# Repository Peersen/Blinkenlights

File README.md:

# Blinkenlights

An Arduino Nano sending DMX to a Driver Chip making several Dimmerchannels blink in a random but controlled manner.
It uses four potentiometers controlling:
- overall Level
- speed of the fading lights
- range how far the lights fade out from Base LEvel
- the amount of lights doing crazy stuff

PCB
- one sided for home-etching
- Dip switch for dmx address
- selector jumper to switch between sending and receiving dmx
- spare poti connectors for later use
- I2C Pins
- reset Pins
- Screw terminals for Vin and 5v rail of the arduino and DMX signal from the SN75176 tranceiverchip

Other projects in this repository help to troubleshoot the main project
- a dmx receiver making six Leds blink
- a softwareSerial receiving arduino that sends received strings to the arduinos USB COM port

To Start
- if you use Platform IO: make sure to change " lib_extra_dirs = D:\ArduinoSketches\libraries" in PlatformIO.ini
- install DMXserial Librarie by Matthias Hertel:
  http://www.mathertel.de/Arduino/DMXSerial.aspx or https://github.com/mathertel/DmxSerial

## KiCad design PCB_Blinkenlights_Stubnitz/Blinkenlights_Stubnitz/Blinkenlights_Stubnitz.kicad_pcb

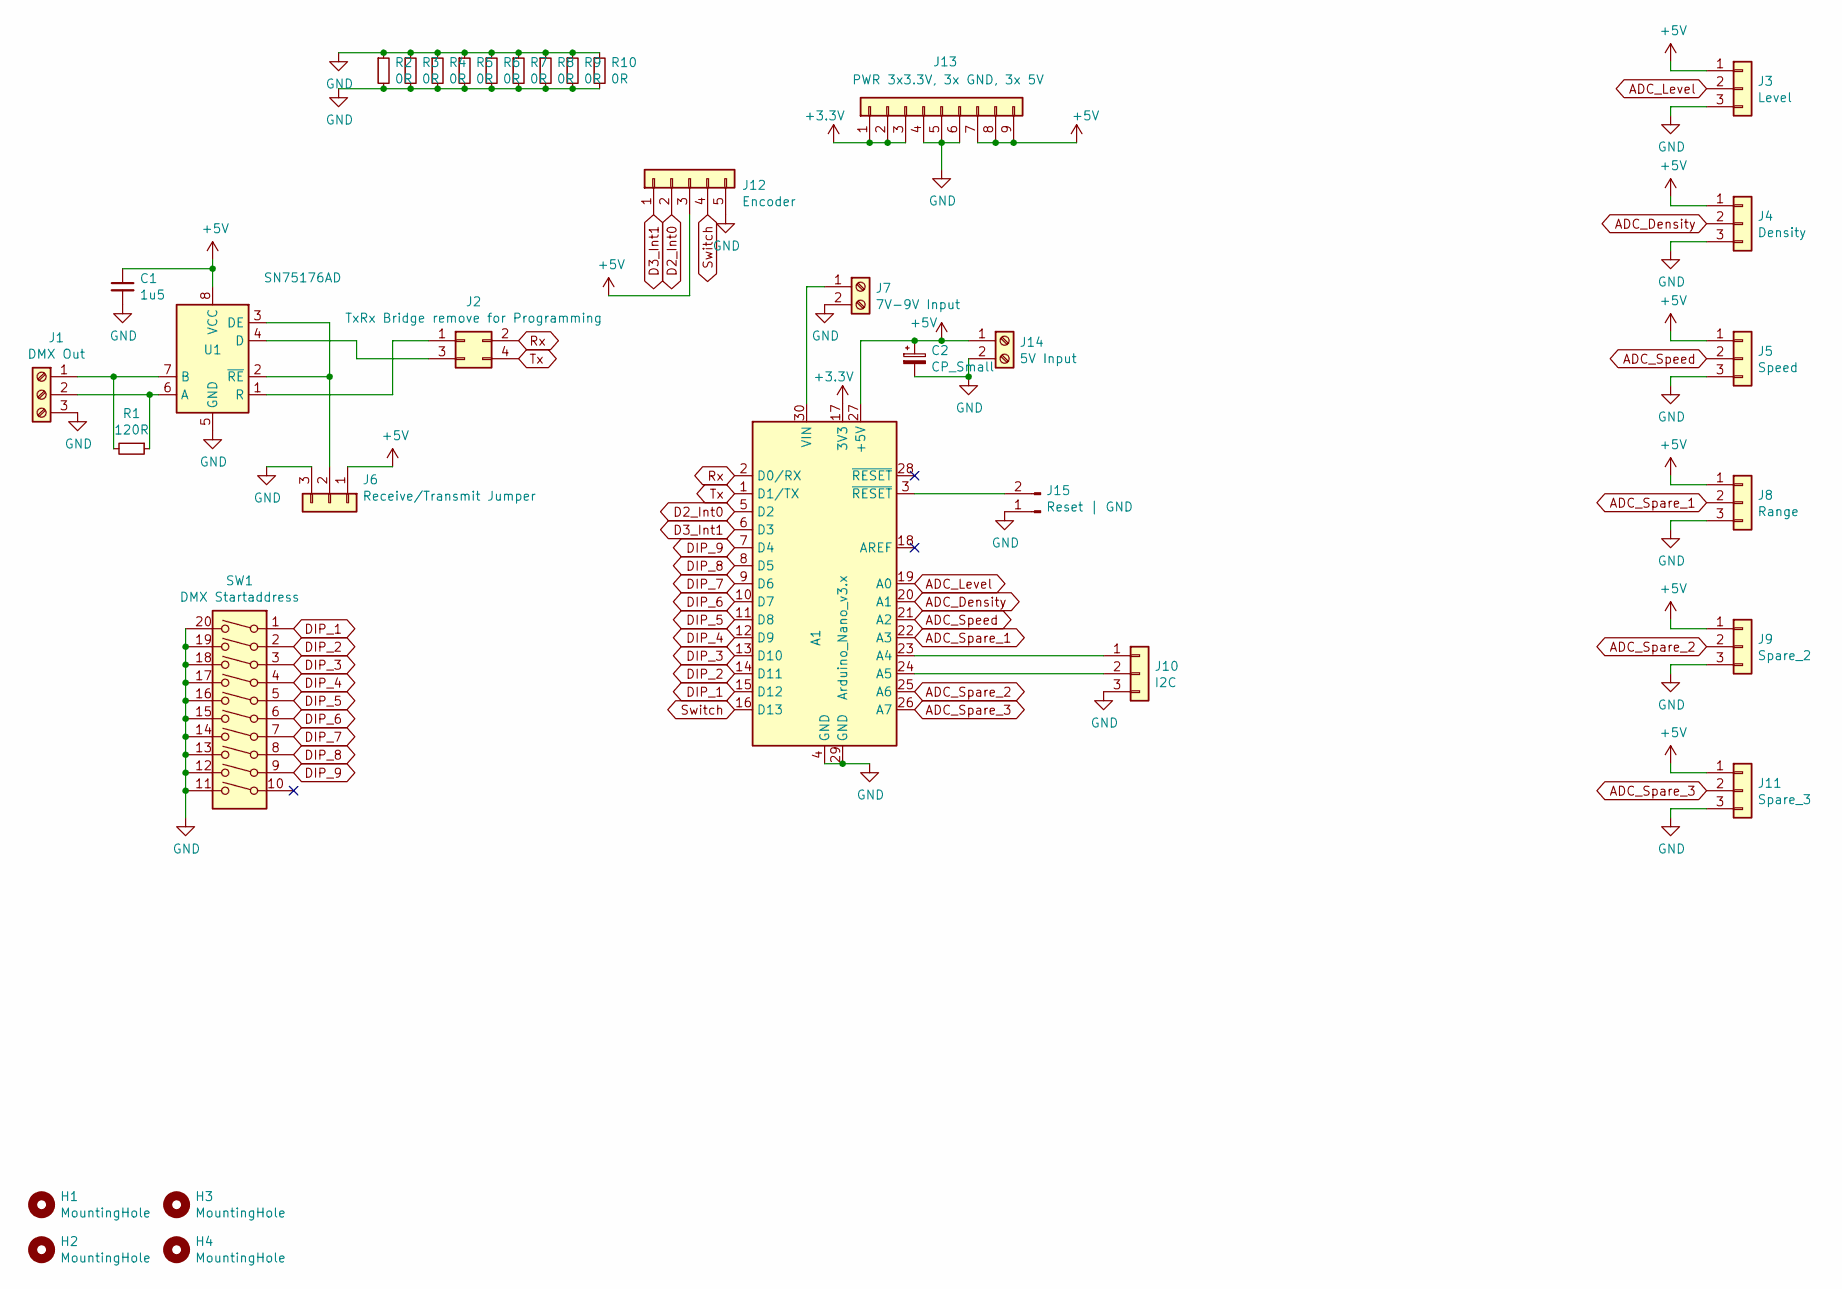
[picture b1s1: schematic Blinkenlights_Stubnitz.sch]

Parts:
A1: Arduino_Nano_v3.x; Arduino_Nano
C1: 1u5; C_1206_3216Metric_Pad1.42x1.75mm_HandSolder
C2: CP_Small; CP_Radial_D5.0mm_P2.50mm
H1, H2, H3, H4: MountingHole; MountingHole_3.2mm_M3_Pad
J1: DMX Out; TerminalBlock_bornier-3_P5.08mm
J2: TxRx Bridge remove for Programming; PinHeader_2x02_P2.54mm_Vertical
J3: Level; PinHeader_1x03_P2.54mm_Vertical
J4: Density; PinHeader_1x03_P2.54mm_Vertical
J5: Speed; PinHeader_1x03_P2.54mm_Vertical
J6: Receive/Transmit Jumper; PinHeader_1x03_P2.54mm_Vertical
J7: 7V-9V Input; TerminalBlock_bornier-2_P5.08mm
J8: Range; PinHeader_1x03_P2.54mm_Vertical
J9: Spare_2; PinHeader_1x03_P2.54mm_Vertical
J10: I2C; PinHeader_1x03_P2.54mm_Vertical
J11: Spare_3; PinHeader_1x03_P2.54mm_Vertical
J12: Encoder; PinHeader_1x05_P2.54mm_Vertical
J13: PWR 3x3.3V, 3x GND, 3x 5V; PinHeader_1x09_P2.54mm_Vertical
J14: 5V Input; TerminalBlock_bornier-2_P5.08mm
J15: Reset | GND; PinHeader_1x02_P2.54mm_Vertical
R1: 120R; R_1206_3216Metric_Pad1.42x1.75mm_HandSolder
R2, R3, R4, R5, R6, R7, R8, R9, R10: 0R; R_Axial_DIN0207_L6.3mm_D2.5mm_P10.16mm_Horizontal
SW1: DMX Startaddress; SW_DIP_SPSTx10_Slide_9.78x27.58mm_W7.62mm_P2.54mm
U1: SN75176AD; SOIC-8_3.9x4.9mm_P1.27mm

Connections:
+3V3: A1.17 (3V3), J13.1, J13.2, J13.3
+5V: A1.27 (+5V), C1.1, C2.1, J3.1, J4.1, J5.1, J6.1, J8.1, J9.1, J11.1, J12.3, J13.7, J13.8, J13.9, J14.1, U1.8 (VCC)
ADC_Density: A1.20 (A1), J4.2
ADC_Level: A1.19 (A0), J3.2
ADC_Spare_1: A1.22 (A3), J8.2
ADC_Spare_2: A1.25 (A6), J9.2
ADC_Spare_3: A1.26 (A7), J11.2
ADC_Speed: A1.21 (A2), J5.2
D2_Int0: A1.5 (D2), J12.2
D3_Int1: A1.6 (D3), J12.1
DIP_1: A1.15 (D12), SW1.1
DIP_2: A1.14 (D11), SW1.2
DIP_3: A1.13 (D10), SW1.3
DIP_4: A1.12 (D9), SW1.4
DIP_5: A1.11 (D8), SW1.5
DIP_6: A1.10 (D7), SW1.6
DIP_7: A1.9 (D6), SW1.7
DIP_8: A1.8 (D5), SW1.8
DIP_9: A1.7 (D4), SW1.9
GND: A1.4 (GND), A1.29 (GND), C1.2, C2.2, J1.3, J3.3, J4.3, J5.3, J6.3, J7.2, J8.3, J9.3, J10.3, J11.3, J12.5, J13.4, J13.5, J13.6, J14.2, J15.1, R2.1, R2.2, R3.1, R3.2, R4.1, R4.2, R5.1, R5.2, R6.1, R6.2, R7.1, R7.2, R8.1, R8.2, R9.1, R9.2, R10.1, R10.2, SW1.11, SW1.12, SW1.13, SW1.14, SW1.15, SW1.16, SW1.17, SW1.18, SW1.19, SW1.20, U1.5 (GND)
unnamed: A1.3 (~RESET), J15.2
unnamed: A1.23 (A4), J10.1
unnamed: A1.24 (A5), J10.2
unnamed: A1.30 (VIN), J7.1
unnamed: J1.1, R1.2, U1.7 (B)
unnamed: J1.2, R1.1, U1.6 (A)
unnamed: J2.1, U1.1 (R)
unnamed: J2.3, U1.4 (D)
unnamed: J6.2, U1.2 (~RE), U1.3 (DE)
Rx: A1.2 (D0/RX), J2.2
Switch: A1.16 (D13), J12.4
Tx: A1.1 (D1/TX), J2.4

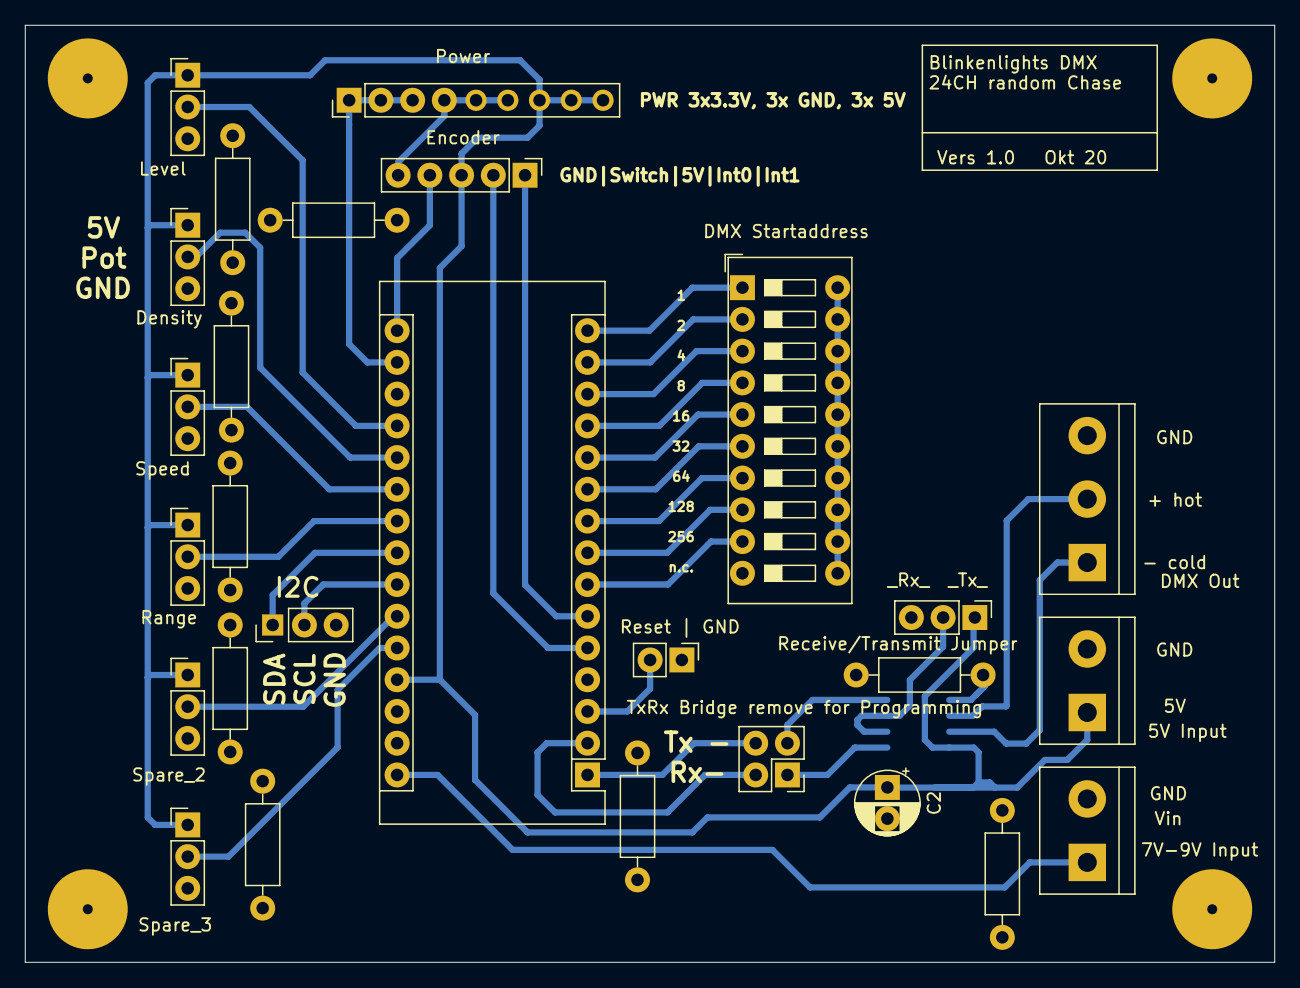
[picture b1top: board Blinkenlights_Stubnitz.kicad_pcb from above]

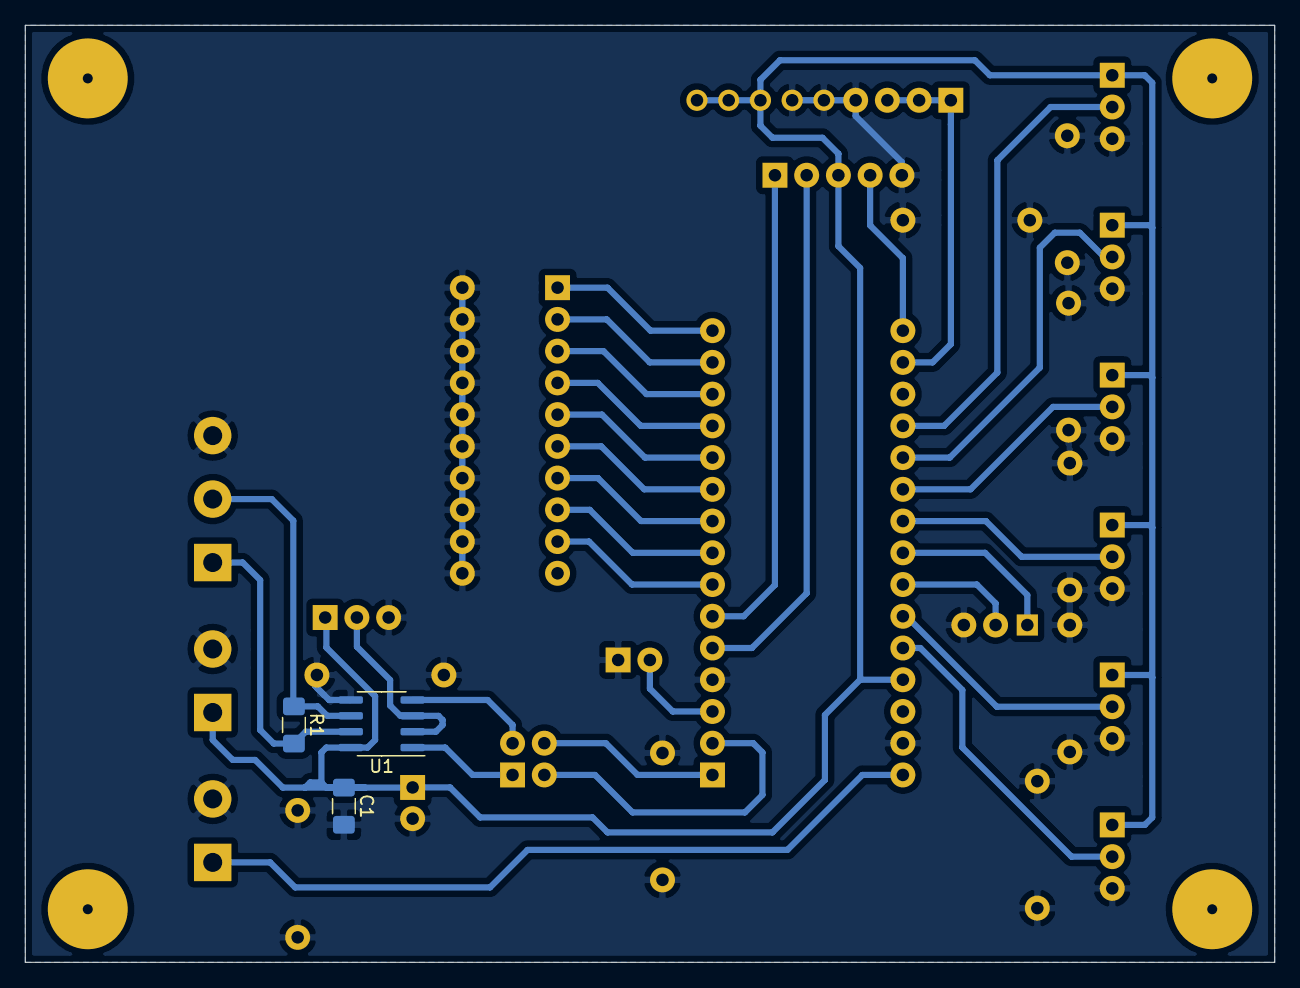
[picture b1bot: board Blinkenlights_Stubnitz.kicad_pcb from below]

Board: 2 copper layers, 100.0 x 75.0 mm, 34 parts (3 on the bottom side), 32 nets.

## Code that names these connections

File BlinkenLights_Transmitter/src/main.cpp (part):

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#define DMX_CONTROLLER true
#define CHANNELS 24

#define ADC_LEVEL A0
#define ADC_DENSITY A1
#define ADC_SPEED A2
#define ADC_SPREAD A3
#define ADC_FLASH_TIME A6 // ADC_Spare_2

#define DIP_1 12
#define DIP_2 11
#define DIP_3 10
#define DIP_4 9
#define DIP_5 8
#define DIP_6 7
#define DIP_7 6
#define DIP_8 5
#define DIP_9 4

#define FLASHMODE_LED 13

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
void setupDIP ()
{
  pinMode(DIP_1, INPUT_PULLUP);
  pinMode(DIP_2, INPUT_PULLUP);
  pinMode(DIP_3, INPUT_PULLUP);
  pinMode(DIP_4, INPUT_PULLUP);
  pinMode(DIP_5, INPUT_PULLUP);
  pinMode(DIP_6, INPUT_PULLUP);
  pinMode(DIP_7, INPUT_PULLUP);
  pinMode(DIP_8, INPUT_PULLUP);
  pinMode(DIP_9, INPUT_PULLUP);
}

int getDMXaddress ()
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
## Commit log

2020-11-02 adding stuff
2020-11-02 schematic as PDF
2020-11-28 added flashtime functionality
    added flashtime functionality
2020-11-28 decomment printf debugging
2020-12-05 added flashmode
